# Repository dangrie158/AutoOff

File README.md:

# AutoOff

A simple timer slightly smarter than a 555 to control 2 individual relays to automatically power off devices after a given amount of time with a single switch.

You can configure the timeout by adjusting the variable `powerOnTime` in the Firmware.

By default a single click on the button will switch on the relays and start the timer.
If the button is pressed again, the timer is stoppend and the relays are opened.
If, however, the button is double-clicked while the relays are on, the timer restarts again.

The PCB is designed for a maximum current flow of 5A / channel, however if you don't need that much current in your application, you should use fuses with a lower, more apropriate rating.

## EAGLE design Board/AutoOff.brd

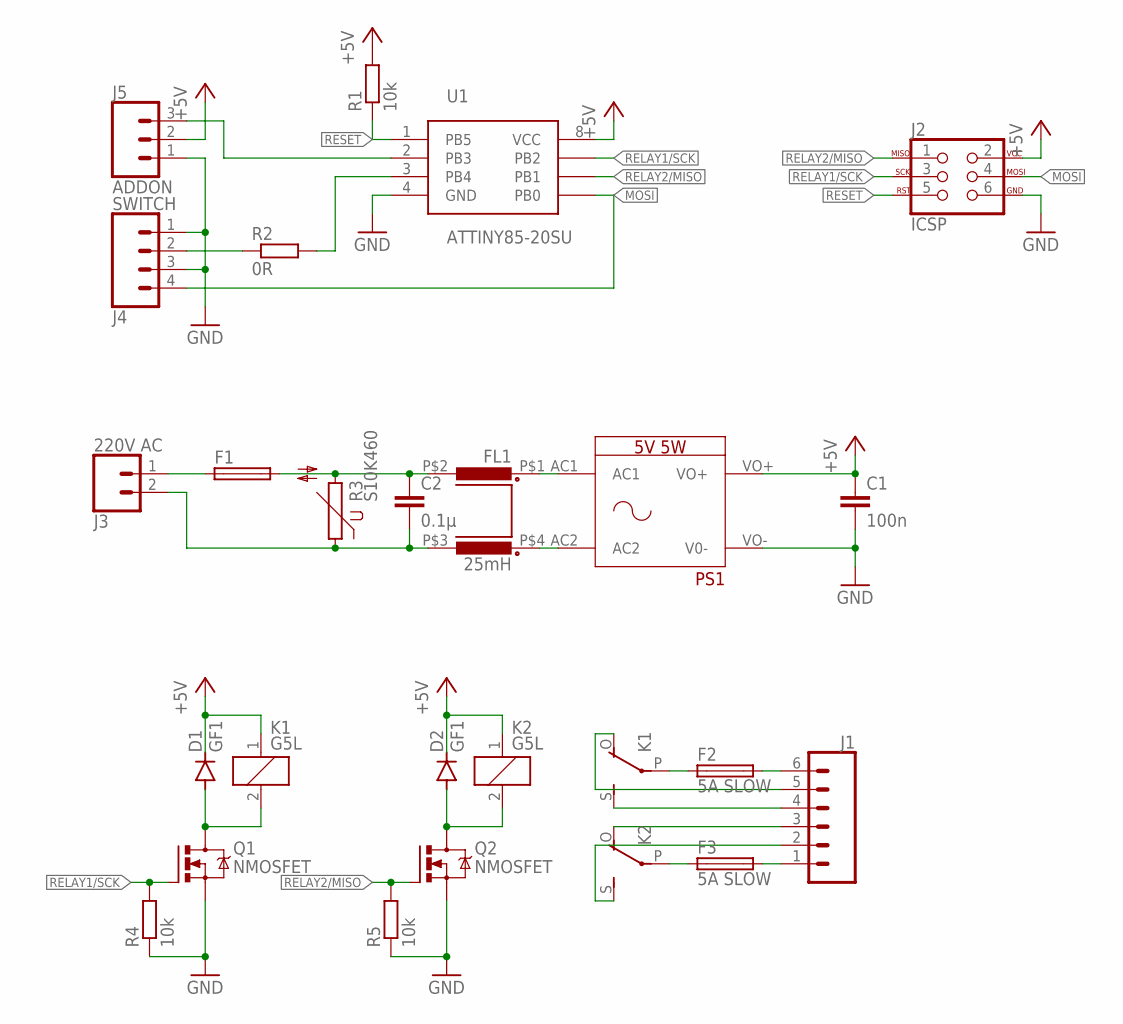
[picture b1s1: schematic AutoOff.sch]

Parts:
C1: 100n; C0603
C2: 0.1µ; C102-064X133
D1, D2: GF1; SMA-DO214AC
F1: 0.5A SLOW; SH22,5A
F2, F3: 5A SLOW; SH22,5A
FL1: 25mH; UU9.8-YH161014
J1: CONN_063.5MM-6; SCREWTERMINAL-3.5MM-6
J2: ICSP; 2X3_LOCK
J3: 220V AC; SCREWTERMINAL-3.5MM-2_LOCK
J4: SWITCH; SCREWTERMINAL-3.5MM-4_LOCK
J5: ADDON; SCREWTERMINAL-3.5MM-3_LOCK.007S
K1, K2: G5L; G5LE
PS1: 5V 5W; HLK-5M
Q1, Q2: NMOSFET; SOT23
R1, R4, R5: 10k; R0603
R2: 0R; R0603
R3: S10K460
U1: ATTINY85-20SU; SOIC-8

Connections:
+5V: C1.1, D1.K (C), D2.K (C), J2.2, J5.2, K1.1, K2.1, PS1.VO+, R1.2, U1.8 (VCC)
GND: C1.2, J2.6, J4.1, J4.3, J5.1, PS1.VO- (V0-), Q1.2 (S), Q2.2 (S), R4.1, R5.1, U1.4 (GND)
MOSI: J2.4, J4.4, U1.5 (PB0)
unnamed: J1.3, K2.O
unnamed: F3.1, K2.P
unnamed: F3.2, J1.1
unnamed: F2.1, K1.P
unnamed: J1.4, K1.S
unnamed: F2.2, J1.6
unnamed: J1.2, K2.S
unnamed: J1.5, K1.O
unnamed: FL1.P$1 (1), PS1.AC1
unnamed: D1.A, K1.2, Q1.3 (D)
unnamed: FL1.P$4 (4), PS1.AC2
unnamed: D2.A, K2.2, Q2.3 (D)
unnamed: J4.2, R2.1
unnamed: R2.2, U1.3 (PB4)
unnamed: J5.3, U1.2 (PB3)
unnamed: F1.1, J3.1
unnamed: C2.2, FL1.P$3 (3), J3.2, R3.1
unnamed: C2.1, F1.2, FL1.P$2 (2), R3.2
RELAY1/SCK: J2.3, Q1.1 (G), R4.2, U1.7 (PB2)
RELAY2/MISO: J2.1, Q2.1 (G), R5.2, U1.6 (PB1)
RESET: J2.5, R1.1, U1.1 (PB5)

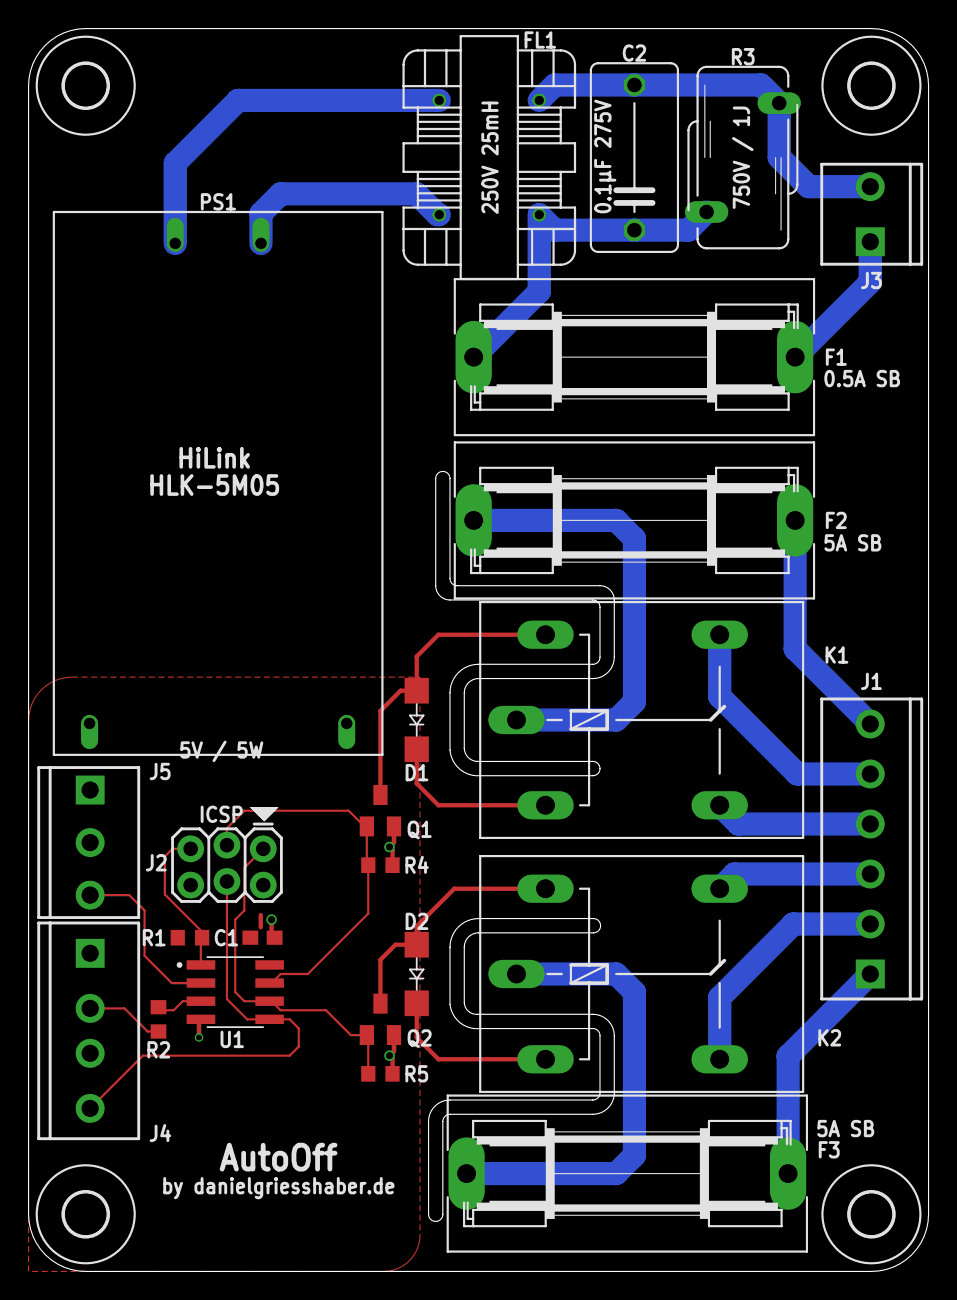
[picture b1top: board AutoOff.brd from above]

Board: 2 copper layers, 63.0 x 87.0 mm, 28 parts (0 on the bottom side), 24 nets.

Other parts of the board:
U$1, U$2, U$3, U$4: 3,0

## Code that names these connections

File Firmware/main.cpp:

#include <stdint.h>
#include <stdlib.h>
#include <stdbool.h>

#include <util/delay.h>
#include <avr/interrupt.h>
#include <avr/io.h>

#include "io.h"

//time the relays will be energized before powering off again
const uint16_t powerOnTime = 60 * 60 * 5;

// time in ms to wait before re-registering a button press for debouncing
const uint8_t debounceDelay = 100;

//time the relays will still be energized (in seconds)
volatile uint16_t timeUntilPowerDown = 0;
volatile bool btnPressed = false;

avr::Input button(avr::PortB, PB0, true, true);
avr::Output relay2(avr::PortB, PB1);
avr::Output relay1(avr::PortB, PB2);
avr::Output addon(avr::PortB, PB3);
avr::Output led(avr::PortB, PB4);

void setupTimer1()
{
    // Setup the Timer1 to fire once a second
    cli();
    // prescaler = FCPU / 16384 ~= 61Hz
    // CTC - clear on compare match with OCR1C
    TCCR1 |= (1 << CTC1);
    TCCR1 |= (1 << CS10) | (1 << CS11) | (1 << CS12) | (1 << CS13);

    // (F_CPU / PRESCALER ) / 1Hz ~= 61
    OCR1A = 61;
    OCR1C = OCR1A;

    // Output Compare Match A Interrupt Enable
    TIMSK |= (1 << OCIE1A);

    // enable interrupts
    sei();
}

void setupInterrupt()
{
    cli();
    // pin change interrupt enable
    GIMSK |= (1 << PCIE);

    // pin change interrupt enabled for PCINT4
    PCMSK |= (1 << PCINT0);

    // enable interrupts
    sei();
}

void debounceButton()
{
    //wait fo the debounce delay before resetting the button state
    _delay_ms(debounceDelay);
    btnPressed = false;
}

int main()
{
    setupTimer1();
    setupInterrupt();

    while (true)
    {
        if (btnPressed)
        {
            if (timeUntilPowerDown == 0)
            {
                // outputs were off, time to switch them on
                led << 1;
                relay1 << 1;
                relay2 << 1;
                timeUntilPowerDown = powerOnTime;
            }
            else
            {
                //switch off the led to indicate we registered the press
                led << 0;
                // outputs are on. start a countdown for power off
                timeUntilPowerDown = 2;

                debounceButton();

                // if the button is pressed again in the next second
                // this was a double press, so rearm the timer
                _delay_ms(1000);
                if (btnPressed)
                {
                    led << 1;
                    timeUntilPowerDown = powerOnTime;
                }
                else
                {
                    //it was not a double-press so interpret it as
                    //a request to power down. (the next if statement
                    // will actually handle the power-down so we don't
                    // need to to anything here)
                }
            }
            debounceButton();
        }

        if (timeUntilPowerDown == 0)
        {
            led << 0;
            relay1 << 0;
            relay2 << 0;
        }
    }
}

ISR(PCINT0_vect)
{
    //only trigger on a high-level of the button
    if (button)
    {
        btnPressed = true;
    }
}

ISR(TIMER1_COMPA_vect)
{
    //decrement the coundown timer
    if (timeUntilPowerDown > 0)
    {
        timeUntilPowerDown--;
    }
}

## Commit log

2020-10-18 added short readme
2020-10-19 moced .vscode directory to Firmware/

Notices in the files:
parts and their libraries:
SparkFun-Connectors: Licensing: Creative Commons ShareAlike 4.0 International - https://creativecommons.org/licenses/by-sa/4.0
